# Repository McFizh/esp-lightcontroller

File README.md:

# ESP32 based led light controller with android client

Repo contains firmware + PCB for ESP32-WROOM-32U based light controller. Repo also has android client written in kotlin. Client discovers the controller on LAN using mDNS.

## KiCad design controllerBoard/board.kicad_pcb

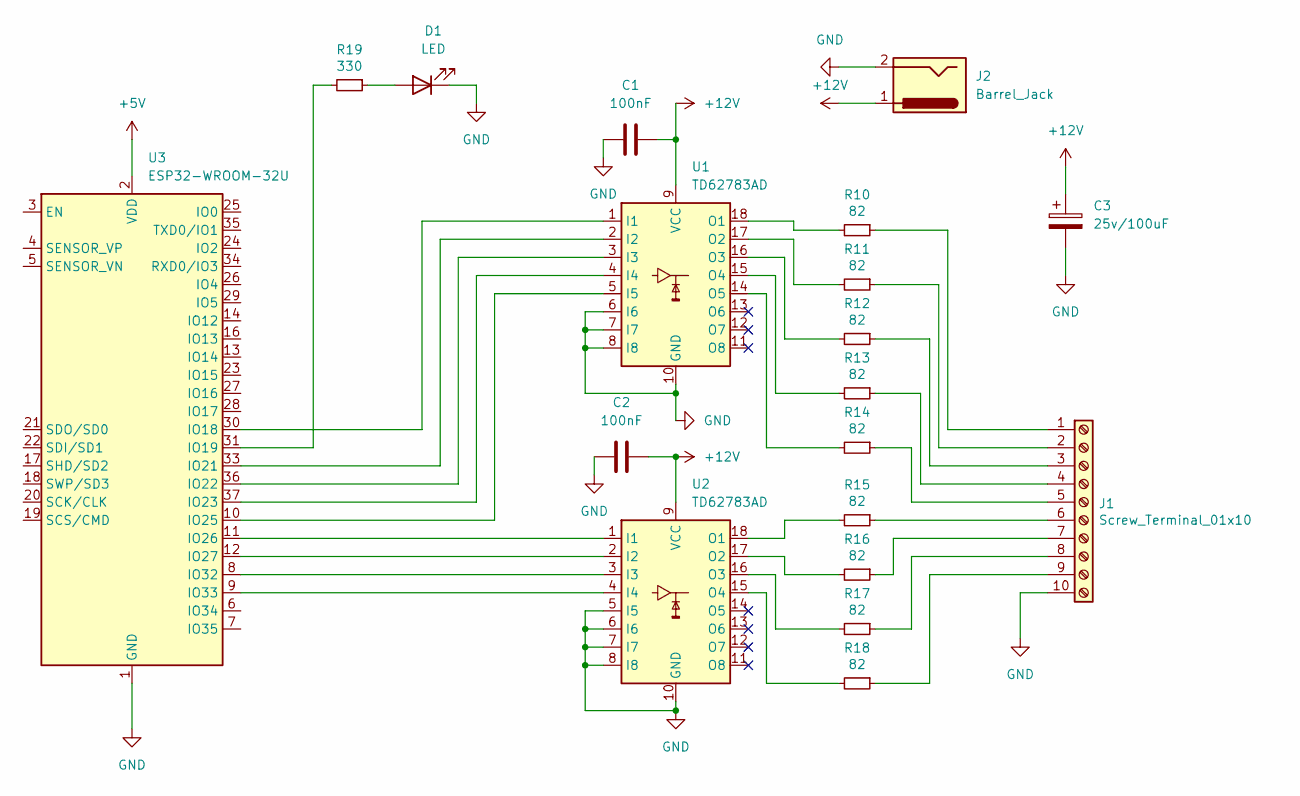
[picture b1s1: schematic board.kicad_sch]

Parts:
C1, C2: 100nF; C_0805_2012Metric_Pad1.18x1.45mm_HandSolder
C3: 25v/100uF; CP_Radial_Tantal_D6.0mm_P5.00mm
D1: LED; LED_0805_2012Metric_Pad1.15x1.40mm_HandSolder
J1: Screw_Terminal_01x10; TerminalBlock_Dinkle_DT-55-B01X-10_P10.00mm
J2: Barrel_Jack; BarrelJack_CUI_PJ-079BH_Horizontal
R10, R11, R12, R13, R14, R15, R16, R17, R18: 82; R_1206_3216Metric
R19: 330; R_1206_3216Metric
U1, U2: TD62783AD; SOP-18_7x12.5mm_P1.27mm
U3: ESP32-WROOM-32U; ESP32-DevKitC

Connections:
+5V: U3.2 (VDD)
+12V: C1.2, C2.2, C3.1, J2.1, U1.9 (VCC), U2.9 (VCC)
GND: C1.1, C2.1, C3.2, D1.1 (K), J1.10, J2.2, U1.6 (I6), U1.7 (I7), U1.8 (I8), U1.10 (GND), U2.5 (I5), U2.6 (I6), U2.7 (I7), U2.8 (I8), U2.10 (GND), U3.1 (GND), U3.15 (GND), U3.38 (GND), U3.39 (GND)
unnamed: D1.2 (A), R19.1
unnamed: J1.1, R10.1
unnamed: J1.2, R11.1
unnamed: J1.3, R12.1
unnamed: J1.4, R13.1
unnamed: J1.5, R14.1
unnamed: J1.6, R15.1
unnamed: J1.7, R16.1
unnamed: J1.8, R17.1
unnamed: J1.9, R18.1
unnamed: U1.1 (I1), U3.30 (IO18)
unnamed: U1.2 (I2), U3.33 (IO21)
unnamed: U1.3 (I3), U3.36 (IO22)
unnamed: U1.4 (I4), U3.37 (IO23)
unnamed: U1.5 (I5), U3.10 (IO25)
unnamed: R10.2, U1.18 (O1)
unnamed: R11.2, U1.17 (O2)
unnamed: R12.2, U1.16 (O3)
unnamed: R13.2, U1.15 (O4)
unnamed: R14.2, U1.14 (O5)
unnamed: U2.1 (I1), U3.11 (IO26)
unnamed: U2.2 (I2), U3.12 (IO27)
unnamed: U2.3 (I3), U3.8 (IO32)
unnamed: U2.4 (I4), U3.9 (IO33)
unnamed: R15.2, U2.18 (O1)
unnamed: R16.2, U2.17 (O2)
unnamed: R17.2, U2.16 (O3)
unnamed: R18.2, U2.15 (O4)
unnamed: R19.2, U3.31 (IO19)

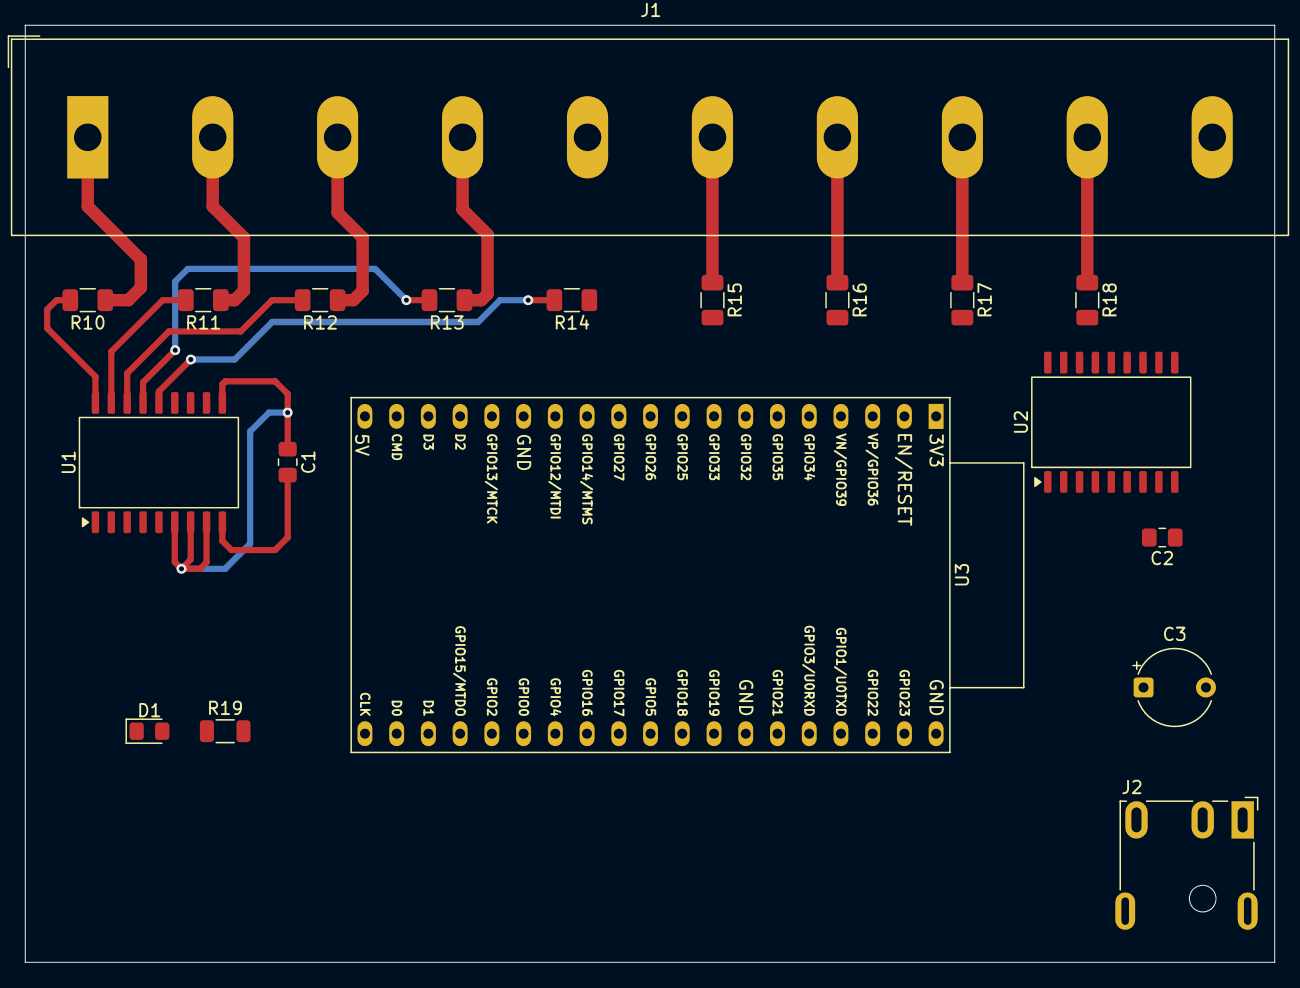
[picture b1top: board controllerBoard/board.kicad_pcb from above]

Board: 2 copper layers, 100.0 x 75.0 mm, 19 parts (0 on the bottom side), 31 nets.

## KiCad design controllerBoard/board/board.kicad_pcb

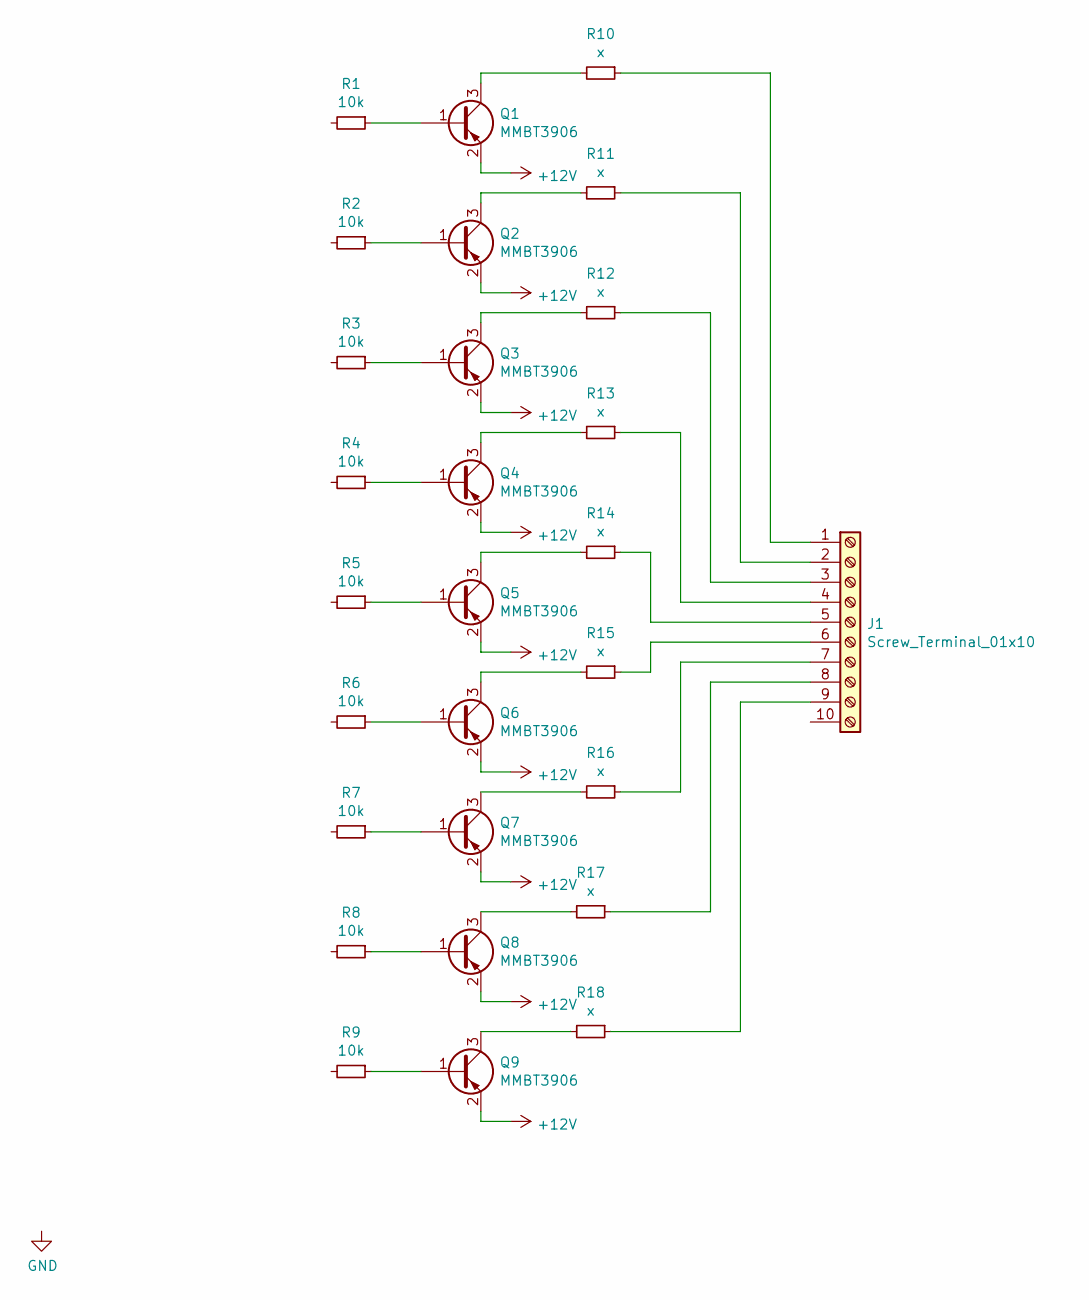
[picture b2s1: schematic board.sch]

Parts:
J1: Screw_Terminal_01x10; TerminalBlock_Dinkle_DT-55-B01X-10_P10.00mm
Q1, Q2, Q3, Q4, Q5, Q6, Q7, Q8, Q9: MMBT3906; SOT-23
R1, R2, R3, R4, R5, R6, R7, R8, R9: 10k; R_1206_3216Metric
R10, R11, R12, R13, R14, R15, R16, R17, R18: x; R_1206_3216Metric

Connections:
+12V: Q1.2 (E), Q2.2 (E), Q3.2 (E), Q4.2 (E), Q5.2 (E), Q6.2 (E), Q7.2 (E), Q8.2 (E), Q9.2 (E)
unnamed: J1.1, R10.1
unnamed: J1.2, R11.1
unnamed: J1.3, R12.1
unnamed: J1.4, R13.1
unnamed: J1.5, R14.1
unnamed: J1.6, R15.1
unnamed: J1.7, R16.1
unnamed: J1.8, R17.1
unnamed: J1.9, R18.1
unnamed: Q1.1 (B), R1.1
unnamed: Q1.3 (C), R10.2
unnamed: Q2.1 (B), R2.1
unnamed: Q2.3 (C), R11.2
unnamed: Q3.1 (B), R3.1
unnamed: Q3.3 (C), R12.2
unnamed: Q4.1 (B), R4.1
unnamed: Q4.3 (C), R13.2
unnamed: Q5.1 (B), R5.1
unnamed: Q5.3 (C), R14.2
unnamed: Q6.1 (B), R6.1
unnamed: Q6.3 (C), R15.2
unnamed: Q7.1 (B), R7.1
unnamed: Q7.3 (C), R16.2
unnamed: Q8.1 (B), R8.1
unnamed: Q8.3 (C), R17.2
unnamed: Q9.1 (B), R9.1
unnamed: Q9.3 (C), R18.2

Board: 2 copper layers, 28 parts (0 on the bottom side), 28 nets, no tracks yet.

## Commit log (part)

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2020-08-05 Initial ESP firmware
2021-12-29 Firmware is now designed for esp32
2021-12-29 Updated android packages
